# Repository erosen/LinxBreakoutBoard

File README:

>>>>>Linx Breakout Board Parts<<<<<

CONSMA002: CONNECTOR FEMALE R/A PCB MT
Datasheet: http://www.linxtechnologies.com/resources/documents/sma_rp-sma_specs.pdf
Package: SMA
Digikey: CONSMA002-ND

RXD-XXX-KH2: LINX RECEIVER / DECODER
Datasheet: http://www.linxtechnologies.com/resources/data-guides/rxd-xxx-kh2.pdf
Package: SMD
Digikey: RXD-315-KH2

219-10MST: 10 POS SWITCH
Datasheet: http://www.ctscorp.com/components/Datasheets/219.pdf
Package: SMD
Digikey: CT21910MST-ND

2X5 Header

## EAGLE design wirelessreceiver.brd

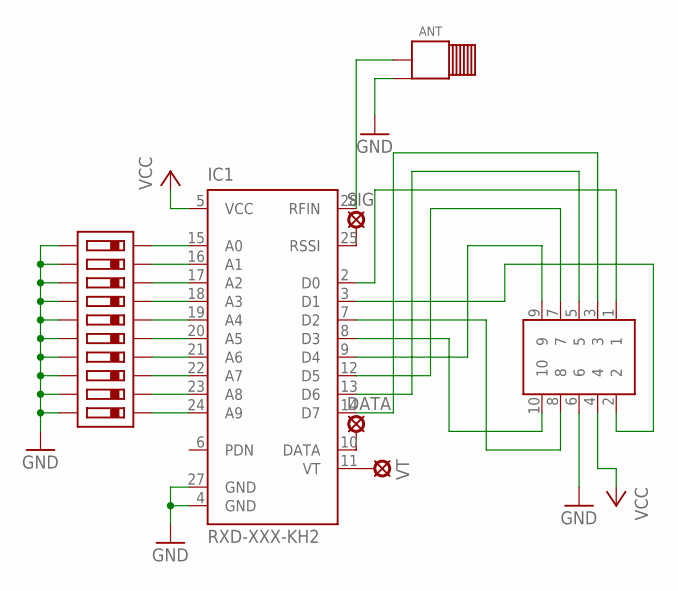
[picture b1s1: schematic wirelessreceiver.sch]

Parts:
ADDR: CT21910MST
ANT: CONSMA002
DATA: MCS10B
IC1: RXD-XXX-KH2
SIG: MCS10B
U$3: 2X5-PHEADER; 2X5-SHROUDED-HEADER
VT: MCS10B

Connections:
A0: ADDR.L9 (A0), IC1.15 (A0)
A1: ADDR.L8 (A1), IC1.16 (A1)
A2: ADDR.L7 (A2), IC1.17 (A2)
A3: ADDR.L6 (A3), IC1.18 (A3)
A4: ADDR.L5 (A4), IC1.19 (A4)
A5: ADDR.L4 (A5), IC1.20 (A5)
A6: ADDR.L3 (A6), IC1.21 (A6)
A7: ADDR.L2 (A7), IC1.22 (A7)
A8: ADDR.L1 (A8), IC1.23 (A8)
A9: ADDR.L0 (A9), IC1.24 (A9)
ANT: ANT.ANT, IC1.28 (RFIN)
D0: IC1.2 (D0), U$3.1
D1: IC1.3 (D1), U$3.2
D2: IC1.7 (D2), U$3.8
D3: IC1.8 (D3), U$3.10
D4: IC1.9 (D4), U$3.9
D5: IC1.12 (D5), U$3.7
D6: IC1.13 (D6), U$3.5
D7: IC1.14 (D7), U$3.3
GND: ADDR.R0 (B9), ADDR.R1 (B8), ADDR.R2 (B7), ADDR.R3 (B6), ADDR.R4 (B5), ADDR.R5 (B4), ADDR.R6 (B3), ADDR.R7 (B2), ADDR.R8 (B1), ADDR.R9 (B0), ANT.GND, ANT.GND1 (GND), ANT.GND2 (GND), ANT.GND3 (GND), IC1.4 (GND), IC1.27 (GND), U$3.6
unnamed: IC1.25 (RSSI), SIG.MP
unnamed: DATA.MP, IC1.10 (DATA)
unnamed: IC1.11 (VT), VT.MP
VCC: IC1.5 (VCC), U$3.4

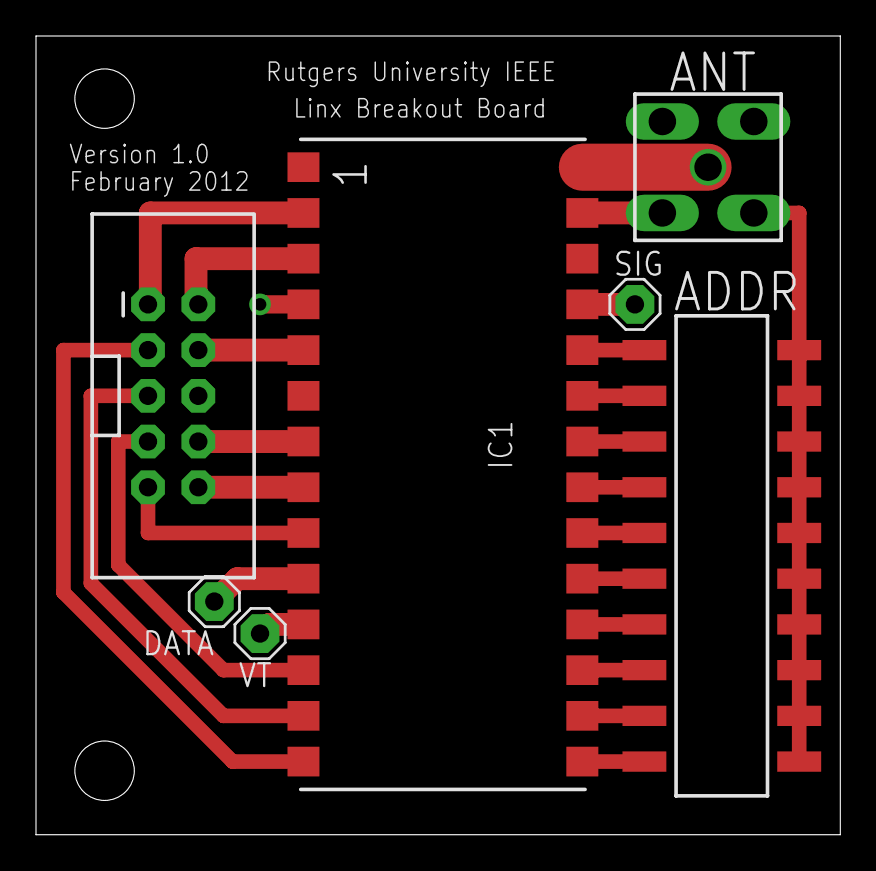
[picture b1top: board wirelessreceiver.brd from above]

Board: 2 copper layers, 44.7 x 44.4 mm, 9 parts (0 on the bottom side), 24 nets.

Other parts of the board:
U$1, U$2: STAND-OFF

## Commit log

2012-02-09 finalized board
2012-02-27 gerber files added

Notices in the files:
parts and their libraries:
SparkFun-Electromechanical: Licensing: CC v3.0 Share-Alike You are welcome to use this library for commercial purposes.
